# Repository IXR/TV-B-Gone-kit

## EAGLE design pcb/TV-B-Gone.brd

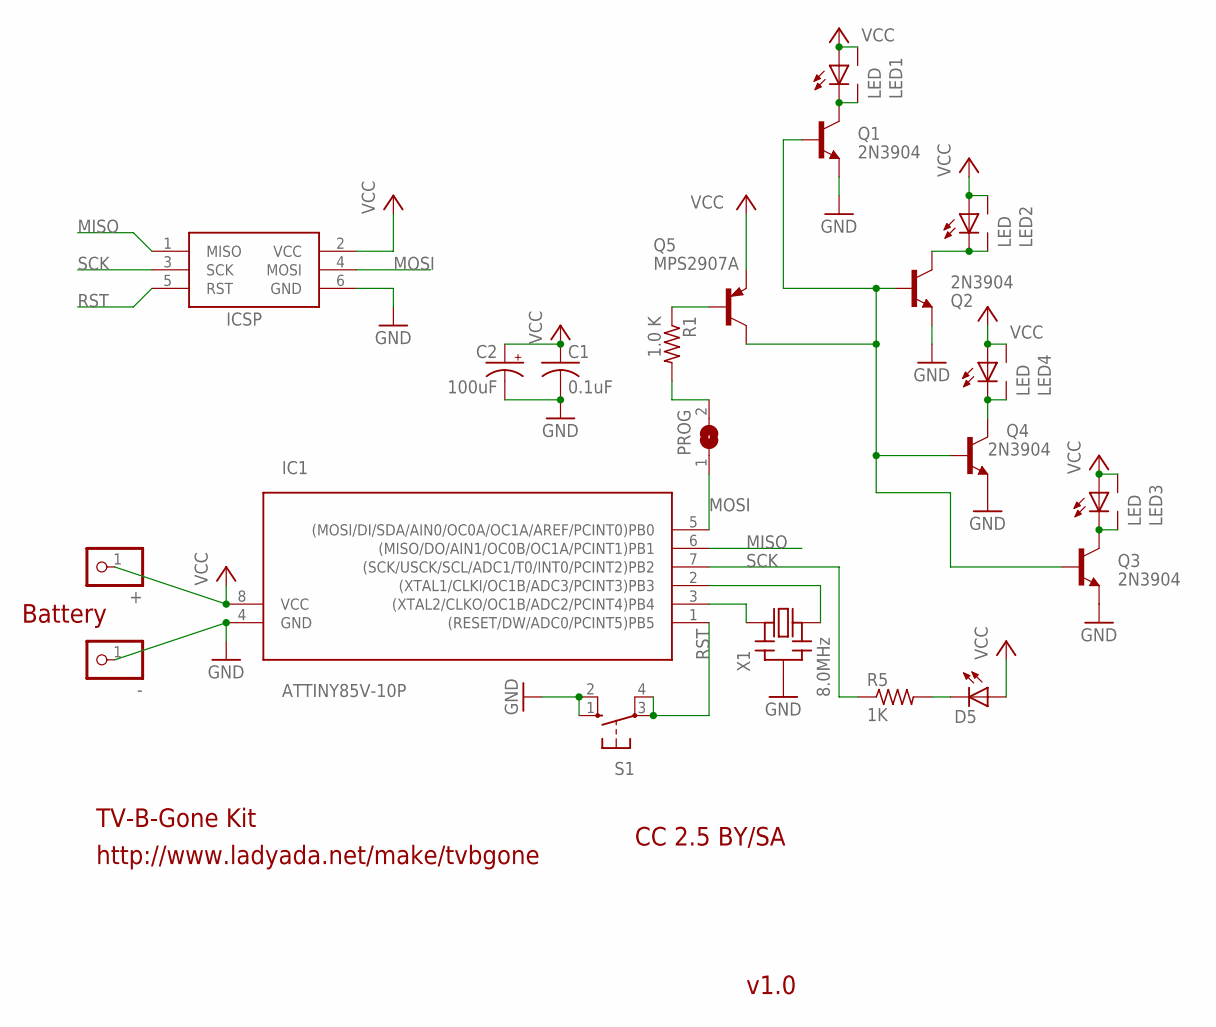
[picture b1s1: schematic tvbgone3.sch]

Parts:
+: PINHD-1X1CB; 1X01-CLEANBIG
-: PINHD-1X1CB; 1X01-CLEANBIG
C1: 0.1uF; C025-025X050
C2: 100uF; E-2.54-0511-HOR
D5: LED3MM
IC1: ATTINY85V-10P; DIL08
ICSP: AVRISP-6; AVRISP
LED1, LED2, LED3, LED4: LED; 5MM-SIDE
PROG: SJ
Q1, Q2, Q3, Q4: 2N3904; TO92-EBC
Q5: MPS2907A; TO92-CBE
R1: 1.0 K; 0207/10
R5: 1K; 0207/10
S1: 10-XX; B3F-10XX
X1: 8.0MHz; CERM_OSC

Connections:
GND: -.1, C1.2, C2.-, IC1.4 (GND), ICSP.6 (GND), Q1.E, Q2.E, Q3.E, Q4.E, S1.1 (S), S1.2 (S1), X1.P$2 (GND)
MISO: IC1.6 ((MISO/DO/AIN1/OC0B/OC1A/PCINT1)PB1), ICSP.1 (MISO)
MOSI: IC1.5 ((MOSI/DI/SDA/AIN0/OC0A/OC1A/AREF/PCINT0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), ICSP.4 (MOSI), PROG.1
unnamed: IC1.3 ((XTAL2/CLKO/OC1B/ADC2/PCINT4)PB4), X1.P$1 (IN)
unnamed: IC1.2 ((XTAL1/CLKI/OC1B/ADC3/PCINT3)PB3), X1.P$3 (OUT)
unnamed: D5.K (C), R5.2
unnamed: Q5.B, R1.1
unnamed: LED4.K (C), LED4.K2 (C1), Q4.C
unnamed: LED2.K (C), LED2.K2 (C1), Q2.C
unnamed: LED3.K (C), LED3.K2 (C1), Q3.C
unnamed: Q1.B, Q2.B, Q3.B, Q4.B, Q5.C
unnamed: LED1.K (C), LED1.K2 (C1), Q1.C
unnamed: PROG.2, R1.2
RST: IC1.1 ((RESET/DW/ADC0/PCINT5)PB5), ICSP.5 (RST), S1.3, S1.4 (P1)
SCK: IC1.7 ((SCK/USCK/SCL/ADC1/T0/INT0/PCINT2)PB2), ICSP.3 (SCK), R5.1
VCC: +.1, C1.1, C2.+, D5.A, IC1.8 (VCC), ICSP.2 (VCC), LED1.A, LED1.A2 (A1), LED2.A, LED2.A2 (A1), LED3.A, LED3.A2 (A1), LED4.A, LED4.A2 (A1), Q5.E

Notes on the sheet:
http://www.ladyada.net/make/tvbgone
TV-B-Gone Kit
v1.0
CC 2.5 BY/SA
Battery

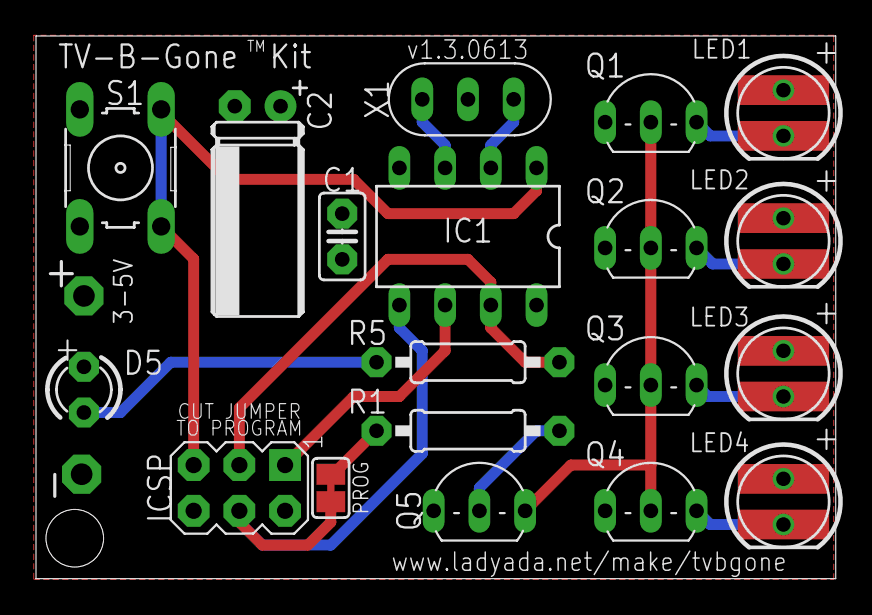
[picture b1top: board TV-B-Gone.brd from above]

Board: 2 copper layers, 44.4 x 30.1 mm, 21 parts (0 on the bottom side), 16 nets.

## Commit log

2013-06-10 Version 1.3.0613
    IXR's updated "EZ Solder" Edition
2013-06-10 Rename tvbgone3.brd to TV-B-Gone.brd
2013-06-10 Rename tvbgone3.sch to TV-B-Gone.sch
